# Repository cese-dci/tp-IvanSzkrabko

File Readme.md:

Shield RS485 para placa MKR1_Wifi1010
================================================

[![CC BY-SA 4.0][cc-by-sa-shield]][cc-by-sa]

This work is licensed under a
[Creative Commons Attribution-ShareAlike 4.0 International License][cc-by-sa].

[![CC BY-SA 4.0][cc-by-sa-image]][cc-by-sa]

[cc-by-sa]: http://creativecommons.org/licenses/by-sa/4.0/
[cc-by-sa-image]: https://licensebuttons.net/l/by-sa/4.0/88x31.png
[cc-by-sa-shield]: https://img.shields.io/badge/License-CC%20BY--SA%204.0-lightgrey.svg

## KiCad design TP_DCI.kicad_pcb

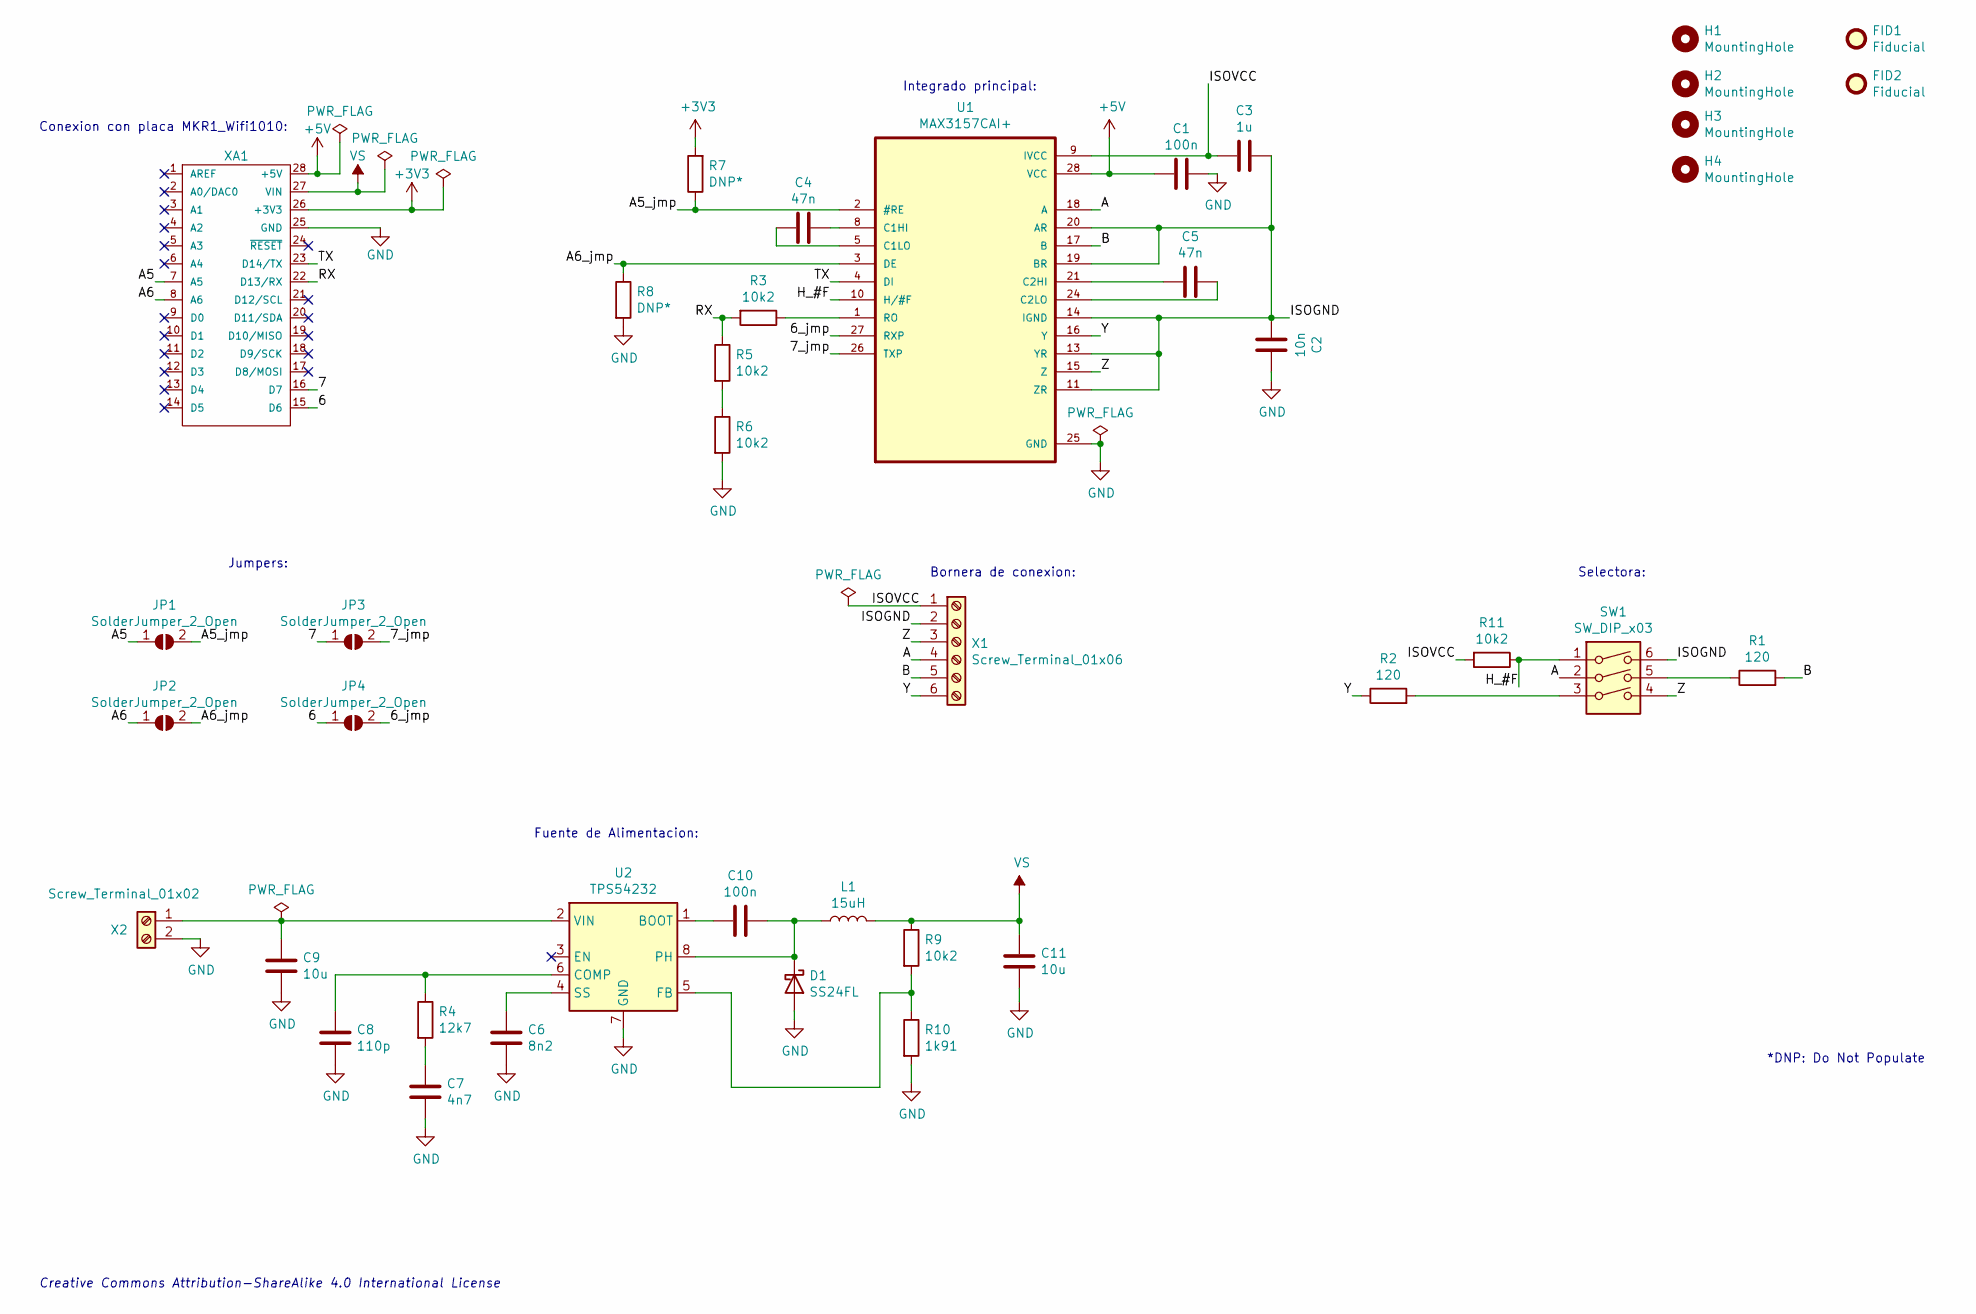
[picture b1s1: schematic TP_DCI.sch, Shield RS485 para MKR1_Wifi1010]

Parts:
C1: 100n; C_0805_2012Metric
C2: 10n; C_0805_2012Metric
C3: 1u; C_0805_2012Metric
C4, C5: 47n; C_0805_2012Metric
C6: 8n2; C_0805_2012Metric
C7: 4n7; C_0805_2012Metric
C8: 110p; CP_EIA-1608-08_AVX-J
C9, C11: 10u; C_0805_2012Metric
C10: 100n; CP_EIA-1608-08_AVX-J
D1: SS24FL; DO-214BA; Mouser 512-SS24FL
FID1, FID2: Fiducial; Fiducial_0.5mm_Mask1.5mm
H1, H2, H3, H4: MountingHole; MountingHole_2.1mm
JP1, JP2, JP3, JP4: SolderJumper_2_Open; SolderJumper-2_P1.3mm_Open_RoundedPad1.0x1.5mm
L1: 15uH; IND_#A921CY-150M=P3; Mouser 710-7447707150
R1, R2: 120; R_0805_2012Metric
R3, R5, R6, R9, R11: 10k2; R_0805_2012Metric
R4: 12k7; R_0805_2012Metric
R7, R8: DNP*; R_0805_2012Metric
R10: 1k91; R_0805_2012Metric
SW1: SW_DIP_x03; SW_DIP_SPSTx03_Slide_6.7x9.18mm_W7.62mm_P2.54mm_LowProfile; Mouser 490-DS01C-254-S-03BE
U1: MAX3157CAI+; SOP65P777X199-28N; Mouser 700-MAX3157CAI+
U2: TPS54232; SOIC-8_3.9x4.9mm_P1.27mm; Mouser 595-TPS54232D
X1: Screw_Terminal_01x06; TerminalBlock_Phoenix_MKDS-1,5-6-5.08_1x06_P5.08mm_Horizont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
X2: Screw_Terminal_01x02; TerminalBlock_bornier-2_P5.08mm
XA1: MKR1_WIFI_1010; MKR_WIFI_1010_Shield

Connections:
+3V3: R7.2, XA1.26 (+3V3)
+5V: C1.1, U1.28 (VCC), XA1.28 (+5V)
/6: JP4.1 (A), XA1.15 (D6)
/6_jmp: JP4.2 (B), U1.27 (RXP)
/7: JP3.1 (A), XA1.16 (D7)
/7_jmp: JP3.2 (B), U1.26 (TXP)
/A: SW1.2, U1.18 (A), X1.4
/A5: JP1.1 (A), XA1.7 (A5)
/A5_jmp: JP1.2 (B), R7.1, U1.2 (#RE)
/A6: JP2.1 (A), XA1.8 (A6)
/A6_jmp: JP2.2 (B), R8.1, U1.3 (DE)
/B: R1.2, U1.17 (B), X1.5
/H_#F: R11.1, SW1.1, U1.10 (H/#F)
/ISOGND: C2.2, C3.2, SW1.6, U1.11 (ZR), U1.13 (YR), U1.14 (IGND), U1.19 (BR), U1.20 (AR), X1.2
/ISOVCC: C3.1, R11.2, U1.9 (IVCC), X1.1
/RX: R3.2, R5.1, XA1.22 (D13/RX)
/TX: U1.4 (DI), XA1.23 (D14/TX)
/Y: R2.1, U1.16 (Y), X1.6
/Z: SW1.4, U1.15 (Z), X1.3
GND: C1.2, C2.1, C6.2, C7.2, C8.2, C9.2, C11.2, D1.2 (A), R6.2, R8.2, R10.2, U1.25 (GND), U2.7 (GND), X2.2, XA1.25 (GND)
unnamed: C4.1, U1.8 (C1HI)
unnamed: C4.2, U1.5 (C1LO)
unnamed: C5.1, U1.24 (C2LO)
unnamed: C5.2, U1.21 (C2HI)
unnamed: C6.1, U2.4 (SS)
unnamed: C7.1, R4.2
unnamed: C8.1, R4.1, U2.6 (COMP)
unnamed: C9.1, U2.2 (VIN), X2.1
unnamed: C10.1, U2.1 (BOOT)
unnamed: C10.2, D1.1 (K), L1.1, U2.8 (PH)
unnamed: R1.1, SW1.5
unnamed: R2.2, SW1.3
unnamed: R3.1, U1.1 (RO)
unnamed: R5.2, R6.1
unnamed: R9.2, R10.1, U2.5 (FB)
VS: C11.1, L1.2, R9.1, XA1.27 (VIN)

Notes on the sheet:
Fuente de Alimentacion:
Integrado principal:
*DNP: Do Not Populate
Conexion con placa MKR1_Wifi1010:
Jumpers:
Selectora:
Bornera de conexion:
Creative Commons Attribution-ShareAlike 4.0 International License

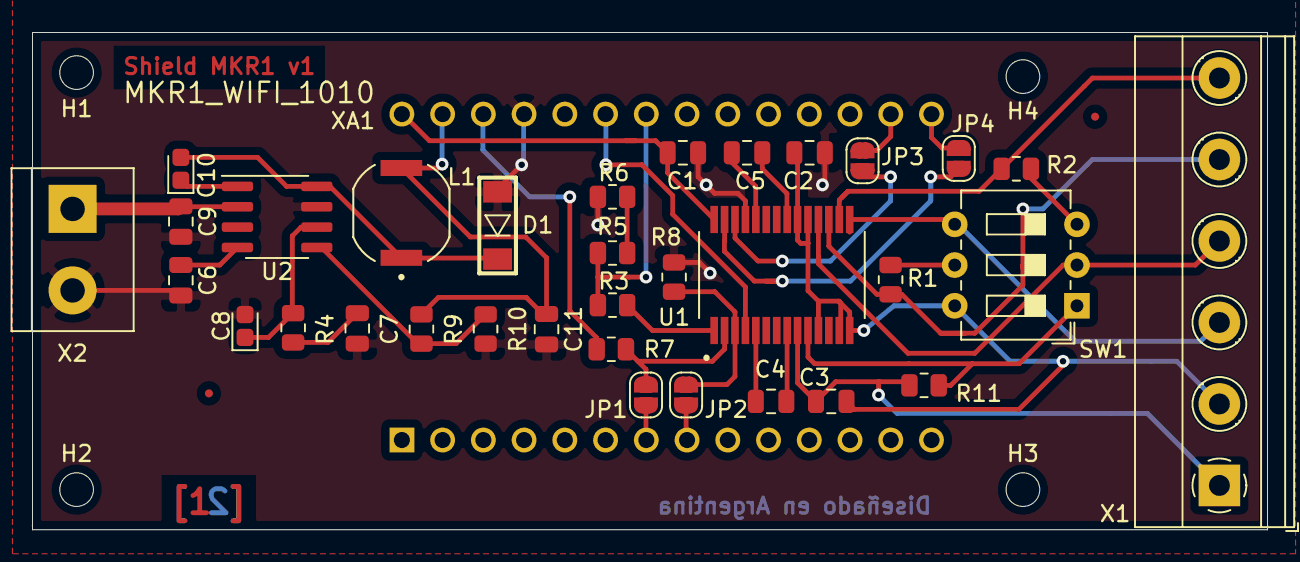
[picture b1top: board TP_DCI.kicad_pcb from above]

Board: 2 copper layers, 77.0 x 31.0 mm, 40 parts (0 on the bottom side), 36 nets.

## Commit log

2021-03-26 avanzo con esquematico
2021-04-09 Avanzo con asociacion de footprints
2021-04-11 Fin etapa 1, esquematico y asociacion de footprints
2021-04-11 Para correccion Etapa 1
2021-04-14 Agrego correcciones de Gaspar
2021-04-14 Agrego gitignore
2021-04-14 .gitignore fix
2021-04-14 Lista para correccion
2021-04-14 Listo para revisar, agrego links a datasheets
2021-04-16 Arranco con el PCB
2021-04-18 Version del PCB completa
2021-04-18 Version para correccion
2021-04-23 Version para corregir PCB
2021-04-24 Listo para correccion
2021-04-28 Agrego correcciones
2021-04-28 Agrego correcciones finales
